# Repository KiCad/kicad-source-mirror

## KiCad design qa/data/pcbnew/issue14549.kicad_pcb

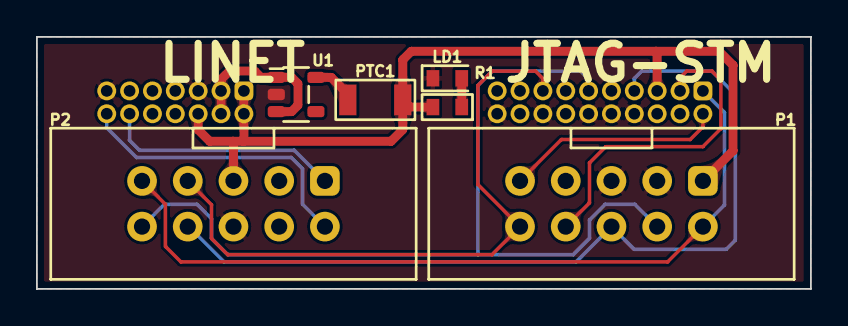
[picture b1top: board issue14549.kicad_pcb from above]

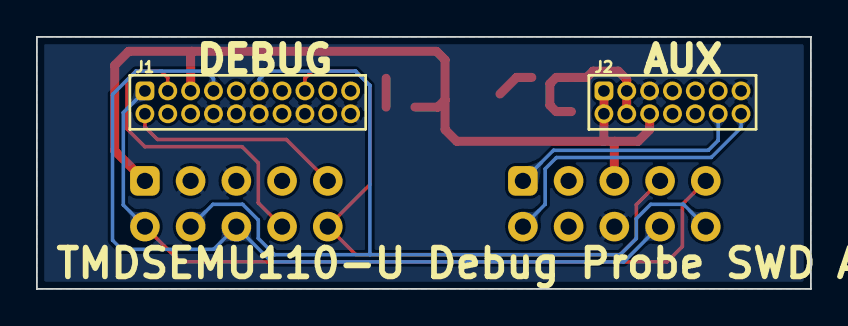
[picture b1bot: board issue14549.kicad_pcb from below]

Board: 2 copper layers, 43.0 x 14.0 mm, 9 parts (3 on the bottom side), 13 nets.

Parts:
J1: 62202021821; J_THT_WR-PHD_62202021821
J2: 62201421821; J_THT_WR-PHD_62201421821
LD1: KPT-1608SGC; LEDC_0603_1608_G
Logo1: WiSER; LOGO_WiSER_Mask
P1, P2: IDC-10P-V; P_THT_IDC-10-V
PTC1: 500mA; PTCF_1206_3216
R1: 1k; RESC_0603_1608X45
U1: MAX40203; SOT23-5

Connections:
+3.3V: J1.5, J2.1, J2.2, J2.6, P1.1, P2.5, PTC1.1, R1.2
/TCK/SWCLK: J1.11, P1.4, P2.10
/TDI: J1.3, P1.8
/TDO/SWO: J1.7, P1.6, P2.8
/TGTSUPPLYOUT: J2.3, J2.4, U1.1, U1.3 (EN)
/TMS/SWDIO: J1.1, P1.2, P2.9
/nRESET: J1.15, P1.10, P2.7
/nTRST: J1.2, P1.9
/tRX: J2.12, P2.1
/tTX: J2.14, P2.2
GND: J1.8, J1.10, J1.12, J1.16, J1.20, J2.5, J2.13, LD1.C, P1.3, P1.5, P2.6, U1.2 (GND)
unnamed: LD1.A, R1.1
unnamed: PTC1.2, U1.5

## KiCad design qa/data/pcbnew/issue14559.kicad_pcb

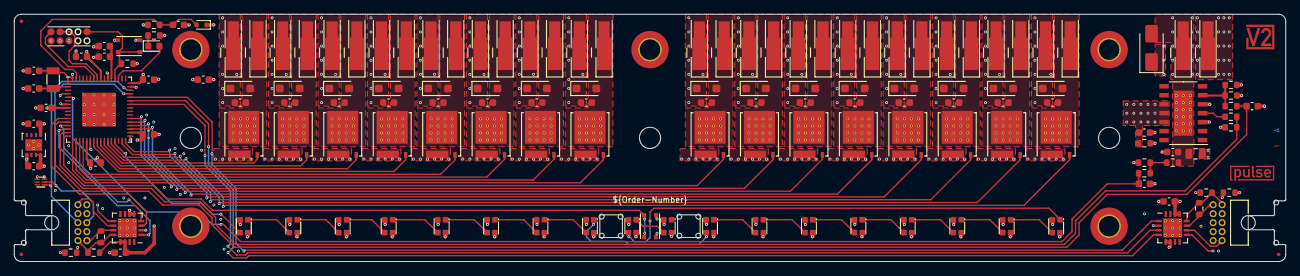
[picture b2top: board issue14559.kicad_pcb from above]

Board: 4 copper layers, 180.0 x 35.0 mm, 171 parts (0 on the bottom side), 87 nets.

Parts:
C101, C102: 18p; C_0603_1608Metric
C103, C105, C112: 10u; C_0603_1608Metric
C106, C107, C108, C109, C110, C111, C201, C301, C401, C501, C601, C701, C801, C901, C1001, C1101, C1201, C1301, C1401, C1501, C1601, C1701, C1801, C1803, C1804, C1805, C1806, C1807, C1901, C2001: 100n; C_0603_1608Metric
C1802: 22u; C_0805_2012Metric
D101, D103, D202, D302, D402, D502, D602, D702, D802, D902, D1002, D1102, D1202, D1302, D1402, D1502, D1602, D1702: WS2812; WS2812-2020
D102: Orange; LED_0603_1608Metric
D201, D301, D401, D501, D601, D701, D801, D901, D1001, D1101, D1201, D1301, D1401, D1501, D1601, D1701: S310FA; D_SOD-123F
D1801: RB501SM; D_SOD-523
ESD101: RCLAMP0582N; SLP1210N6
FID101, FID102, FID103: Fiducial; Fiducial_0.5mm_Mask1mm_Paste
H101, H102, H103: MountingHole_3mm
ICON101: Board_pulse; Board_pulse_Small
ICON102: V2-logo; Logo_Small
INFO101: ORDER-NUMBER; Order_Number
INFO102: Layer_Numbers
J101: CORTEX-DEBUG; Cortex_Debug_Pad
J201, J202, J301, J302, J401, J402, J501, J502, J601, J602, J701, J702, J801, J802, J901, J902, J1001, J1002, J1101, J1102, J1201, J1202, J1301, J1302, J1401, J1402, J1501, J1502, J1601, J1602, J1701, J1702, J1801, J1802: WAGO-2065; 2065-100
J1901, J2001: 2x05_Horizontal; PinHeader_2x05_P1.27mm_Horizontal
PLUG101, PLUG102: PCB_Plug_Horizontal
Q201, Q301, Q401, Q501, Q601, Q701, Q801, Q901, Q1001, Q1101, Q1201, Q1301, Q1401, Q1501, Q1601, Q1701: BSC010N04LS; TDSON-8-FL
R101, R1801, R1806, R1807: 100k; R_0603_1608Metric
R102: 330R; R_0603_1608Metric
R1802, R1803, R1808, R1810, R1902, R1903, R2002, R2003: 10k; R_0603_1608Metric
R1804, R1805: 2k7; R_0603_1608Metric
R1809: 100R; R_0603_1608Metric
R1901, R2001: 120R; R_0603_1608Metric
SPACER101, SPACER102, SPACER103, SPACER104, SPACER105: 9774030243
SW101, SW102: SW_Push; SKSG
SWB101: Button-bottom; PCB_Button-bottom
TVS1801: SMAJ24CA; D_SMA
U102: ATSAMD51J; QFN-64-1EP_9x9mm_P0.5mm_EP4.8x4.8mm_ThermalVias
U103: TPS78433QWDRBRQ1; VSON-8-1_3x3mm_P0.65_EP1.65x2.4mm
U1801: BTT6010; PG-TDS0-14
U1902, U2002: SN65MLVD203B; WQFN-16-1EP_4x4mm_P0.65mm_EP2.7x2.7mm_ThermalVias
Y101: 32.768kHz; Crystal_SMD_3215-2Pin_3.2x1.5mm

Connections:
+3V3: C107.1, C108.1, C109.1, C110.1, C111.1, C112.1, C1901.1, C2001.1, J101.1 (VCC), R101.1, R1809.1, R1902.1, R2002.1, U102.4 (ANAREF), U102.8 (VDDANA), U102.21 (VDDIOB), U102.34 (VDDIO), U102.48 (VDDIO), U102.56 (VDDIO), U103.1 (OUT), U1801.5 (DEN), U1902.13 (VCC), U1902.14 (VCC), U2002.13 (VCC), U2002.14 (VCC)
+5V: C103.1, D101.4 (VCC), D103.4 (VCC), D202.4 (VCC), D302.4 (VCC), D402.4 (VCC), D502.4 (VCC), D602.4 (VCC), D702.4 (VCC), D802.4 (VCC), D902.4 (VCC), D1002.4 (VCC), D1102.4 (VCC), D1202.4 (VCC), D1302.4 (VCC), D1402.4 (VCC), D1502.4 (VCC), D1602.4 (VCC), D1702.4 (VCC), ESD101.6 (VBUS), J1901.4, J1901.7, J2001.4, J2001.7, U103.7 (EN), U103.8 (IN)
+24V: C201.1, C301.1, C401.1, C501.1, C601.1, C701.1, C801.1, C901.1, C1001.1, C1101.1, C1201.1, C1301.1, C1401.1, C1501.1, C1601.1, C1701.1, C1804.1, C1805.1, D201.1 (K), D301.1 (K), D401.1 (K), D501.1 (K), D601.1 (K), D701.1 (K), D801.1 (K), D901.1 (K), D1001.1 (K), D1101.1 (K), D1201.1 (K), D1301.1 (K), D1401.1 (K), D1501.1 (K), D1601.1 (K), D1701.1 (K), D1801.1 (K), J201.1, J301.1, J401.1, J501.1, J601.1, J701.1, J801.1, J901.1, J1001.1, J1101.1, J1201.1, J1301.1, J1401.1, J1501.1, J1601.1, J1701.1, R1806.1, U1801.10 (OUT), U1801.11 (OUT), U1801.12 (OUT)
/Button: SW101.2, U102.16 (PA07)
/Current-Sense: C1801.1, R1802.1, U102.12 (PB09)
/LED1: D202.3 (IN), U102.29 (PA12)
/LED5: D502.1 (OUT), D602.3 (IN)
/LED9: D902.1 (OUT), D1002.3 (IN)
/LED13: D1102.1 (OUT), D1402.3 (IN)
/LED-Button: D101.3 (IN), D1502.1 (OUT)
/LED-onboard: D102.2 (A), U102.51 (PA27)
/Link Plug/RX-A: J1901.9, R1901.1, R1902.2, U1902.12 (A)
/Link Plug/RX-B: J1901.10, R1901.2, R1903.1, U1902.11 (B)
/Link Plug/TX-Y: J1901.2, U1902.9 (Y)
/Link Plug/TX-Z: J1901.1, U1902.10 (Z)
/Link Socket/RX-A: J2001.9, R2001.1, R2002.2, U2002.12 (A)
/Link Socket/RX-B: J2001.10, R2001.2, R2003.1, U2002.11 (B)
/Link Socket/TX-Y: J2001.2, U2002.9 (Y)
/Link Socket/TX-Z: J2001.1, U2002.10 (Z)
/PWM1: Q201.4 (G), U102.26 (PB13)
/PWM2: Q301.4 (G), U102.25 (PB12)
/PWM3: Q401.4 (G), U102.24 (PB11)
/PWM4: Q501.4 (G), U102.23 (PB10)
/PWM5: Q601.4 (G), U102.20 (PA11)
/PWM6: Q701.4 (G), U102.19 (PA10)
/PWM7: Q801.4 (G), U102.18 (PA09)
/PWM8: Q901.4 (G), U102.17 (PA08)
/PWM9: Q1001.4 (G), U102.38 (PA19)
/PWM10: Q1301.4 (G), U102.37 (PA18)
/PWM11: Q1201.4 (G), U102.36 (PA17)
/PWM12: Q1101.4 (G), U102.35 (PA16)
/PWM13: Q1401.4 (G), U102.32 (PA15)
/PWM14: Q1701.4 (G), U102.31 (PA14)
/PWM15: Q1601.4 (G), U102.28 (PB15)
/PWM16: Q1501.4 (G), U102.27 (PB14)
/PWM Channel 1/LED-Out: D202.1 (OUT), D302.3 (IN)
/PWM Channel 1/PWM-Sink: C201.2, D201.2 (A), J202.1, Q201.5 (D)
/PWM Channel 2/LED-Out: D302.1 (OUT), D402.3 (IN)
/PWM Channel 2/PWM-Sink: C301.2, D301.2 (A), J302.1, Q301.5 (D)
/PWM Channel 3/LED-Out: D402.1 (OUT), D502.3 (IN)
/PWM Channel 3/PWM-Sink: C401.2, D401.2 (A), J402.1, Q401.5 (D)
/PWM Channel 4/PWM-Sink: C501.2, D501.2 (A), J502.1, Q501.5 (D)
/PWM Channel 5/LED-Out: D602.1 (OUT), D702.3 (IN)
/PWM Channel 5/PWM-Sink: C601.2, D601.2 (A), J602.1, Q601.5 (D)
/PWM Channel 6/LED-Out: D702.1 (OUT), D802.3 (IN)
/PWM Channel 6/PWM-Sink: C701.2, D701.2 (A), J702.1, Q701.5 (D)
/PWM Channel 7/LED-Out: D802.1 (OUT), D902.3 (IN)
/PWM Channel 7/PWM-Sink: C801.2, D801.2 (A), J802.1, Q801.5 (D)
/PWM Channel 8/PWM-Sink: C901.2, D901.2 (A), J902.1, Q901.5 (D)
/PWM Channel 9/PWM-Sink: C1001.2, D1001.2 (A), J1002.1, Q1001.5 (D)
/PWM Channel 10/LED-In: D1002.1 (OUT), D1302.3 (IN)
/PWM Channel 10/LED-Out: D1202.3 (IN), D1302.1 (OUT)
/PWM Channel 10/PWM-Sink: C1301.2, D1301.2 (A), J1302.1, Q1301.5 (D)
/PWM Channel 11/LED-Out: D1102.3 (IN), D1202.1 (OUT)
/PWM Channel 11/PWM-Sink: C1201.2, D1201.2 (A), J1202.1, Q1201.5 (D)
/PWM Channel 12/PWM-Sink: C1101.2, D1101.2 (A), J1102.1, Q1101.5 (D)
/PWM Channel 13/LED-Out: D1402.1 (OUT), D1702.3 (IN)
/PWM Channel 13/PWM-Sink: C1401.2, D1401.2 (A), J1402.1, Q1401.5 (D)
/PWM Channel 14/LED-Out: D1602.3 (IN), D1702.1 (OUT)
/PWM Channel 14/PWM-Sink: C1701.2, D1701.2 (A), J1702.1, Q1701.5 (D)
/PWM Channel 15/LED-Out: D1502.3 (IN), D1602.1 (OUT)
/PWM Channel 15/PWM-Sink: C1601.2, D1601.2 (A), J1602.1, Q1601.5 (D)
/PWM Channel 16/PWM-Sink: C1501.2, D1501.2 (A), J1502.1, Q1501.5 (D)
/Plug-RX: U102.14 (PA05), U1902.1 (R)
/Plug-TX: U102.13 (PA04), U1902.4 (D)
/Plug-TX-Enable: U102.11 (PB08), U1902.3 (DE)
/Power +24V/+24V-Supply: C1802.1, C1803.1, J1801.1, R1807.1, TVS1801.2 (A), U1801.15 (VS)
/Power +24V/IN: R1803.1, U1801.4 (IN)
/Power +24V/IS: R1802.2, R1804.1, R1805.1, U1801.6 (IS)
/Power-Enable: R1801.2, R1803.2, U102.15 (PA06)
/RESET: J101.10 (RESET), R101.2, SW102.2, U102.52 (~RESET)
/Resistance-Sense: C1806.1, D1801.2 (A), R1809.2, U102.63 (PB02)
/SWCLK: J101.4 (SWCLK), U102.57 (PA30)
/SWDIO: J101.2 (SWDIO), U102.58 (PA31)
/Socket-RX: U102.44 (PA23), U2002.1 (R)
/Socket-TX: U102.43 (PA22), U2002.4 (D)
/Socket-TX-Enable: U102.42 (PA21), U2002.3 (DE)
/USB+: ESD101.4 (I/O1), J1901.5, U102.46 (USB+)
/USB-: ESD101.5 (I/O2), J1901.6, U102.45 (USB-)
/VDDCORE: C105.1, C106.1, U102.53 (VDDCORE)
/Voltage-Sense: C1807.1, R1810.2, U102.5 (PB04)
/XIN32: C101.1, U102.1 (PA00), Y101.1
/XOUT32: C102.1, U102.2 (PA01), Y101.2
GND: C101.2, C102.2, C103.2, C105.2, C106.2, C107.2, C108.2, C109.2, C110.2, C111.2, C112.2, C1801.2, C1802.2, C1803.2, C1804.2, C1805.2, C1806.2, C1807.2, C1901.2, C2001.2, D101.2 (GND), D103.2 (GND), D202.2 (GND), D302.2 (GND), D402.2 (GND), D502.2 (GND), D602.2 (GND), D702.2 (GND), D802.2 (GND), D902.2 (GND), D1002.2 (GND), D1102.2 (GND), D1202.2 (GND), D1302.2 (GND), D1402.2 (GND), D1502.2 (GND), D1602.2 (GND), D1702.2 (GND), ESD101.1 (GND), J101.3 (GND), J101.5 (GND), J1802.1, J1901.3, J1901.8, J2001.3, J2001.8, Q201.1 (S), Q301.1 (S), Q401.1 (S), Q501.1 (S), Q601.1 (S), Q701.1 (S), Q801.1 (S), Q901.1 (S), Q1001.1 (S), Q1101.1 (S), Q1201.1 (S), Q1301.1 (S), Q1401.1 (S), Q1501.1 (S), Q1601.1 (S), Q1701.1 (S), R102.2, R1801.1, R1804.2, R1805.2, R1806.2, R1808.2, R1903.2, R2003.2, SPACER101.1, SPACER102.1, SPACER103.1, SPACER104.1, SPACER105.1, SW101.1, SW102.1, TVS1801.1 (K), U102.7 (GNDANA), U102.22 (GND), U102.33 (GND), U102.47 (GND), U102.54 (GND), U102.64 (GPIOIN), U102.65 (PAD), U103.5 (GND), U103.9 (GND), U1801.3 (GND), U1902.2 (RE), U1902.5 (GND), U1902.6 (GND), U1902.17 (GND), U2002.2 (RE), U2002.5 (GND), U2002.6 (GND), U2002.17 (GND)
unnamed: D101.1 (OUT), D103.3 (IN)
unnamed: D102.1 (K), R102.1
unnamed: R1807.2, R1808.1, R1810.1
